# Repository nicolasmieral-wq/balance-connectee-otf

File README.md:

# Balance connectée pour la caisse Ouvretaferme

Ce petit script relie une balance de marché à la **caisse enregistreuse d'[Ouvretaferme](https://www.ouvretaferme.org)**. On pose le produit, on touche l'article dans la caisse, et le poids s'inscrit et s'enregistre tout seul.

Il ne modifie pas le site Ouvretaferme, n'utilise pas son API et ne demande aucune clé. Il s'ajoute simplement à la page de la caisse, ouverte dans le navigateur, à l'aide d'un favori.

> [!WARNING]
> **Projet expérimental, à usage de test uniquement.**
> Il ne doit pas être utilisé pour la vente directe ni pour aucune vente au poids. Le poids transmis à la caisse ne remplace pas une pesée faite et affichée par un instrument de pesage homologué, et la réglementation de la métrologie légale encadre ce type de transmission.
> Ce logiciel est fourni « tel quel », sans aucune garantie. **L'auteur n'est pas responsable** de son utilisation, en particulier pour de la vente directe, ni des erreurs de poids, de prix ou d'encaissement qui pourraient en résulter. Toute personne qui l'utilise pour vendre le fait sous sa seule responsabilité.

> Projet indépendant, créé par un maraîcher, sans lien officiel avec Ouvretaferme. Une mise à jour de la caisse peut l'empêcher de fonctionner : vérifiez toujours le montant avant d'encaisser.

## Ce qui a été testé

| Élément | Testé avec | État |
|---|---|---|
| Balance | Elicom S300FM 15/30, en transmission continue | ✅ Fonctionne |
| Liaison Bluetooth | Adaptateur DSD TECH SH-B30-BLE (RS-232 vers Bluetooth Low Energy) | ✅ Fonctionne |
| Téléphone | Samsung Galaxy A14, Android 14, Chrome | ✅ Fonctionne |
| iPad | Navigateur Bluefy | ❌ Pas encore : la recherche Bluetooth est refusée (code 2) |
| USB direct | Câble DSD TECH SH-RJ12B (puce CP2102N) sur Android | ⚠️ Code présent, jamais validé en réel |

D'autres balances peuvent fonctionner si elles envoient le même format de trame : voir [Autres balances](docs/AUTRES-BALANCES.md).

## Comment ça marche

```
Balance ──RS-232──> SH-B30-BLE ──Bluetooth──> Chrome sur Android ──> caisse Ouvretaferme
```

1. La balance envoie son poids environ une fois par seconde, par exemple `P+000.245` pour 245 g.
2. Le module SH-B30-BLE transmet ce texte en Bluetooth.
3. Le script, lancé sur la page de la caisse, lit le poids et l'affiche dans un petit bandeau en haut.
4. Quand vous ouvrez un article vendu **au kilo**, il saisit le poids stable dans « Vendu » et touche **Enregistrer**.

## Les sécurités

- **Poids stable uniquement :** un poids en mouvement, négatif ou en surcharge n'est jamais saisi.
- **Mesure récente :** une mesure de plus de 2,5 secondes est refusée, et une déconnexion efface le dernier poids.
- **Correction respectée :** si « Vendu » contient déjà une valeur, le script n'écrit rien. Vous pouvez corriger à la main ou toucher **Poids**.
- **Pas de double pesée :** entre deux articles, le poids doit changer d'au moins 5 g ou repasser par zéro. Pratique pour peser plusieurs produits dans le même panier.
- **Articles à la pièce ignorés :** le script n'agit que si l'unité est le kilo.
- **Montant contrôlé :** si la caisse ne calcule pas le montant, le script n'enregistre pas.

## Matériel

- Une balance compatible, réglée en transmission continue à 9600 bauds (voir [Câblage et réglages](docs/CABLAGE.md)).
- Un adaptateur **DSD TECH SH-B30-BLE** et son alimentation 5 V.
- Un câble à fabriquer, de la prise RJ de la balance vers une prise **DB9 femelle**.
- Un téléphone ou une tablette **Android**, avec **Chrome** à jour.

## Installation

### 1. Héberger le script

Le script doit être accessible en ligne, à une adresse en `https://`. Deux possibilités :

- **Sur votre propre site** : déposez `balance-otf.js` sur votre hébergement, par exemple par FTP. C'est la méthode testée.
- **Depuis ce dépôt, via jsDelivr**, sans hébergement : `https://cdn.jsdelivr.net/gh/nicolasmieral-wq/balance-connectee-otf@<version>/balance-otf.js`. Remplacez `<version>` par le numéro d'un commit précis (par exemple `c3dd12bd`), pour que le script ne change pas sans que vous le sachiez. Le fichier y est bien servi, mais cette méthode n'a pas encore été essayée dans la caisse.

### 2. Créer le favori

Dans Chrome sur un ordinateur, synchronisé avec le même compte Google que le téléphone :

1. Ouvrez le gestionnaire de favoris (Ctrl+Maj+O) et ajoutez un favori nommé **Balance OTF**.
2. Dans le champ URL, collez la ligne ci-dessous, en remplaçant l'adresse par celle de votre script :

```
javascript:void(document.head.appendChild(document.createElement('script')).src='https://VOTRE-SITE/balance-otf.js?v='+Date.now())
```

Chrome sur Android refuse souvent qu'on colle une ligne aussi longue : c'est pourquoi on passe par l'ordinateur et la synchronisation. Le `Date.now()` force le chargement de la dernière version à chaque lancement.

### 3. Lancer le script sur la caisse

1. Sur le téléphone, ouvrez une vente dans la caisse Ouvretaferme.
2. Touchez la barre d'adresse, effacez-la, tapez `Balance OTF` et touchez la **suggestion du favori**. Le lancer depuis la liste des favoris ne fonctionne pas.
3. Un petit bandeau apparaît en haut. Touchez **Bluetooth** et choisissez **SH-B30-BLE**.

Il faut relancer le favori à chaque rechargement de la page.

## Utilisation

- **Bandeau du haut :** le poids actuel, le bouton **Bluetooth** (masqué une fois relié), **Auto** et **×** pour retirer le script.
- **Auto (vert) :** posez le produit, touchez l'article, c'est enregistré.
- **Auto (gris) :** mode manuel. Ouvrez l'article et touchez **Poids**, sous « Vendu », puis **Enregistrer**.

Utilisez-le uniquement sur une ferme ou une vente de test, jamais pour une vraie vente.

## Documentation

- [Câblage et réglages](docs/CABLAGE.md)
- [Dépannage](docs/DEPANNAGE.md)
- [Autres balances et protocoles](docs/AUTRES-BALANCES.md)

## Pour les développeurs

Le script est un seul fichier sans dépendance. Les tests se lancent avec Node.js :

```
node tests/balance-otf.test.js
```

Ils couvrent le décodage des trames, les règles de mesure, le Bluetooth et l'USB simulés. Le comportement dans la vraie caisse ne peut se vérifier qu'à la main.

Points d'appui dans la page de la caisse, à revoir si Ouvretaferme change son interface :

- champ « Vendu » : `input[name^="number["]` dans `.merchant-field` ;
- montant : `input[name="price[ID]"]` ;
- passage en saisie clavier : `.merchant-switch-keyboard-link`. Le pavé tactile limite à 2 décimales et ne recalcule pas le montant.

## Licence et responsabilité

[MIT](LICENSE). Projet expérimental, sans garantie : l'auteur décline toute responsabilité en cas d'utilisation pour la vente, directe ou non.

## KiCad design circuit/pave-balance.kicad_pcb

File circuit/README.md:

# Circuit imprimé du pavé balance (prototype)

> **Prototype non fabriqué, non testé.** Contrôles KiCad 10 : 0 erreur, 0 connexion manquante, schéma et circuit identiques. Réservé aux essais, jamais à la vente (voir l'avertissement du [README principal](../README.md)).

Circuit 62,6 × 84,6 mm, 2 couches, pistes 0,3 mm, isolement 0,2 mm (0,25 mm mesuré), vias 0,6/0,3 mm. Composants traversants, faciles à souder.

## Composants

| Repère | Composant | Empreinte KiCad |
|---|---|---|
| SW1-SW16 | Boutons 12 × 12 mm + capuchons carrés | Button_Switch_THT:SW_PUSH-12mm (pastilles réduites à 2,2 mm) |
| U1 | MAX3232 en DIP-16 (support conseillé) | Package_DIP:DIP-16_W7.62mm |
| C1-C5 | Condensateurs céramique 100 nF, pas de 2,5 mm | Capacitor_THT:C_Disc_D3.0mm_W1.6mm_P2.50mm |
| R1 | Résistance 330 Ω | Resistor_THT:R_Axial_DIN0207… |
| D1 | LED 3 mm | LED_THT:LED_D3.0mm |
| J1 | Prise RJ12 Amphenol 54601 (6P6C), **montée dessous** | Connector_RJ:RJ12_Amphenol_54601 |
| J2, J3 | Barrettes 1 × 7 au pas de 2,54 mm, pour le XIAO ESP32-S3 **suspendu dessous** | Connector_PinHeader_2.54mm:PinHeader_1x07 |
| H1-H4 | Trous M2,5 | — |

## Connexions

- Pavé 4 × 4 en matrice, sans diodes : lignes sur D0-D3, colonnes sur D4, D5, D6, D10.
- RJ12 broche 5 → MAX3232 R1IN → R1OUT → D7 ; broche 4 → R2IN → R2OUT → D8 ; broche 3 → masse. Émetteurs non câblés : rien n'est envoyé à la balance.
- LED sur D9 par R1. MAX3232 alimenté en 3,3 V par le XIAO.

## À vérifier avant de commander

- Écart entre les deux rangées de broches du XIAO (15,24 mm retenu) : mesurer au pied à coulisse.
- Longueur des barrettes du XIAO (environ 14 mm entre le XIAO et le circuit).
- Hauteur des boutons et capuchons par rapport au couvercle (circuit à z = 17, dessous du couvercle à z = 26).
- Sens d'ouverture de la prise RJ12 (vers le bord avant).

## Fichiers

| Fichier | Rôle |
|---|---|
| `pave-balance.kicad_pro/.kicad_sch/.kicad_pcb` | Projet KiCad (s'ouvre dans KiCad 8 à 10) |
| `pave.kicad_sym`, `sym-lib-table` | Symboles du schéma |
| `generer_pcb.py` | Régénère schéma, placement et routage (Python 3 + numpy) |
| `verifier.py` | Contrôle indépendant des isolements et de la continuité |
| `rendu_pcb.py` | Dessine `apercu.png` |

## Fabrication

Fichier prêt : `pave-balance-gerbers.zip` (Gerber + perçage, généré par KiCad 10). Pour le refaire dans KiCad : *Fichiers → Fabrication → Gerbers*, puis *Générer fichiers de perçage*. Compresser le dossier obtenu en ZIP et l'envoyer au fabricant. Réglages courants : 2 couches, 1,6 mm, finition HASL.

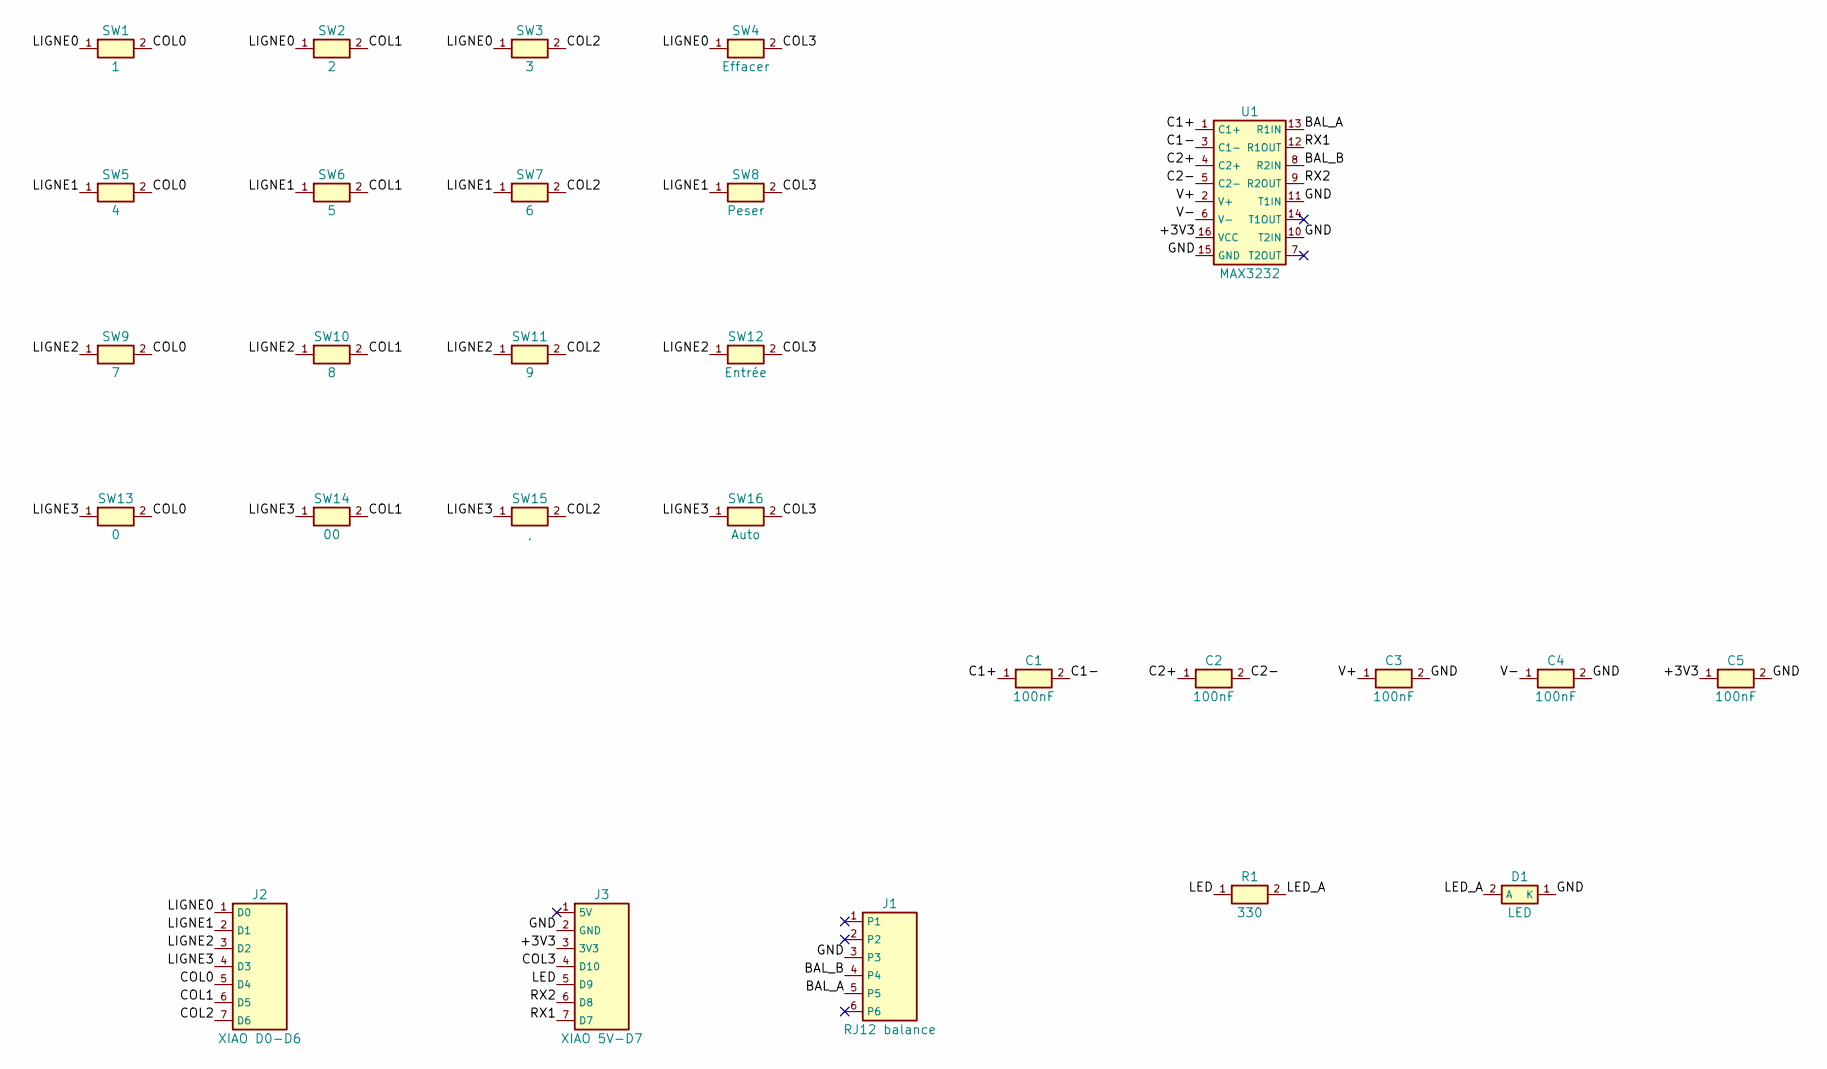
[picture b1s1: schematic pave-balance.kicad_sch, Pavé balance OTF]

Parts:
C1, C2, C3, C4, C5: 100nF; C_Disc_D3.0mm_W1.6mm_P2.50mm
D1: LED; LED_D3.0mm
J1: RJ12 balance; RJ12_Amphenol_54601
J2: XIAO D0-D6; PinHeader_1x07_P2.54mm_Vertical
J3: XIAO 5V-D7; PinHeader_1x07_P2.54mm_Vertical
R1: 330; R_Axial_DIN0207_L6.3mm_D2.5mm_P7.62mm_Horizontal
SW1: 1; SW_PUSH-12mm
SW2: 2; SW_PUSH-12mm
SW3: 3; SW_PUSH-12mm
SW4: Effacer; SW_PUSH-12mm
SW5: 4; SW_PUSH-12mm
SW6: 5; SW_PUSH-12mm
SW7: 6; SW_PUSH-12mm
SW8: Peser; SW_PUSH-12mm
SW9: 7; SW_PUSH-12mm
SW10: 8; SW_PUSH-12mm
SW11: 9; SW_PUSH-12mm
SW12: Entrée; SW_PUSH-12mm
SW13: 0; SW_PUSH-12mm
SW14: 00; SW_PUSH-12mm
SW15: ,; SW_PUSH-12mm
SW16: Auto; SW_PUSH-12mm
U1: MAX3232; DIP-16_W7.62mm

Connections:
/+3V3: C5.1, J3.3 (3V3), U1.16 (VCC)
/BAL_A: J1.5, U1.13 (R1IN)
/BAL_B: J1.4, U1.8 (R2IN)
/C1+: C1.1, U1.1 (C1+)
/C1-: C1.2, U1.3 (C1-)
/C2+: C2.1, U1.4 (C2+)
/C2-: C2.2, U1.5 (C2-)
/COL0: J2.5 (D4), SW1.2, SW5.2, SW9.2, SW13.2
/COL1: J2.6 (D5), SW2.2, SW6.2, SW10.2, SW14.2
/COL2: J2.7 (D6), SW3.2, SW7.2, SW11.2, SW15.2
/COL3: J3.4 (D10), SW4.2, SW8.2, SW12.2, SW16.2
/GND: C3.2, C4.2, C5.2, D1.1 (K), J1.3, J3.2 (GND), U1.10 (T2IN), U1.11 (T1IN), U1.15 (GND)
/LED: J3.5 (D9), R1.1
/LED_A: D1.2 (A), R1.2
/LIGNE0: J2.1 (D0), SW1.1, SW2.1, SW3.1, SW4.1
/LIGNE1: J2.2 (D1), SW5.1, SW6.1, SW7.1, SW8.1
/LIGNE2: J2.3 (D2), SW9.1, SW10.1, SW11.1, SW12.1
/LIGNE3: J2.4 (D3), SW13.1, SW14.1, SW15.1, SW16.1
/RX1: J3.7 (D7), U1.12 (R1OUT)
/RX2: J3.6 (D8), U1.9 (R2OUT)
/V+: C3.1, U1.2 (V+)
/V-: C4.1, U1.6 (V-)

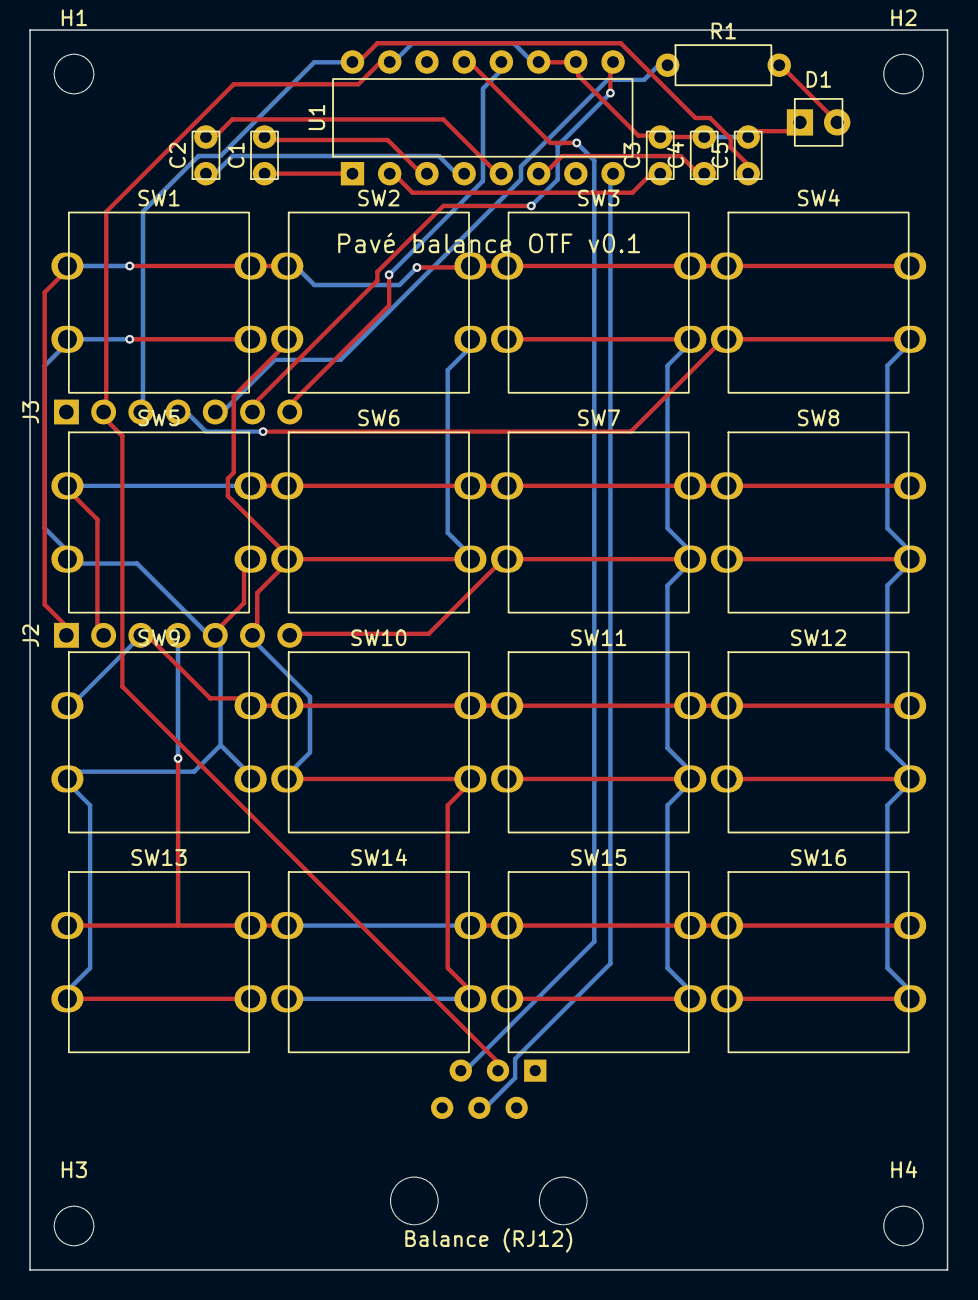
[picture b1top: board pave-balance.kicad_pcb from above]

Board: 2 copper layers, 62.6 x 84.6 mm, 31 parts (1 on the bottom side), 22 nets.

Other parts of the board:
H1, H2, H3, H4: M2.5; MountingHole_2.7mm_M2.5
